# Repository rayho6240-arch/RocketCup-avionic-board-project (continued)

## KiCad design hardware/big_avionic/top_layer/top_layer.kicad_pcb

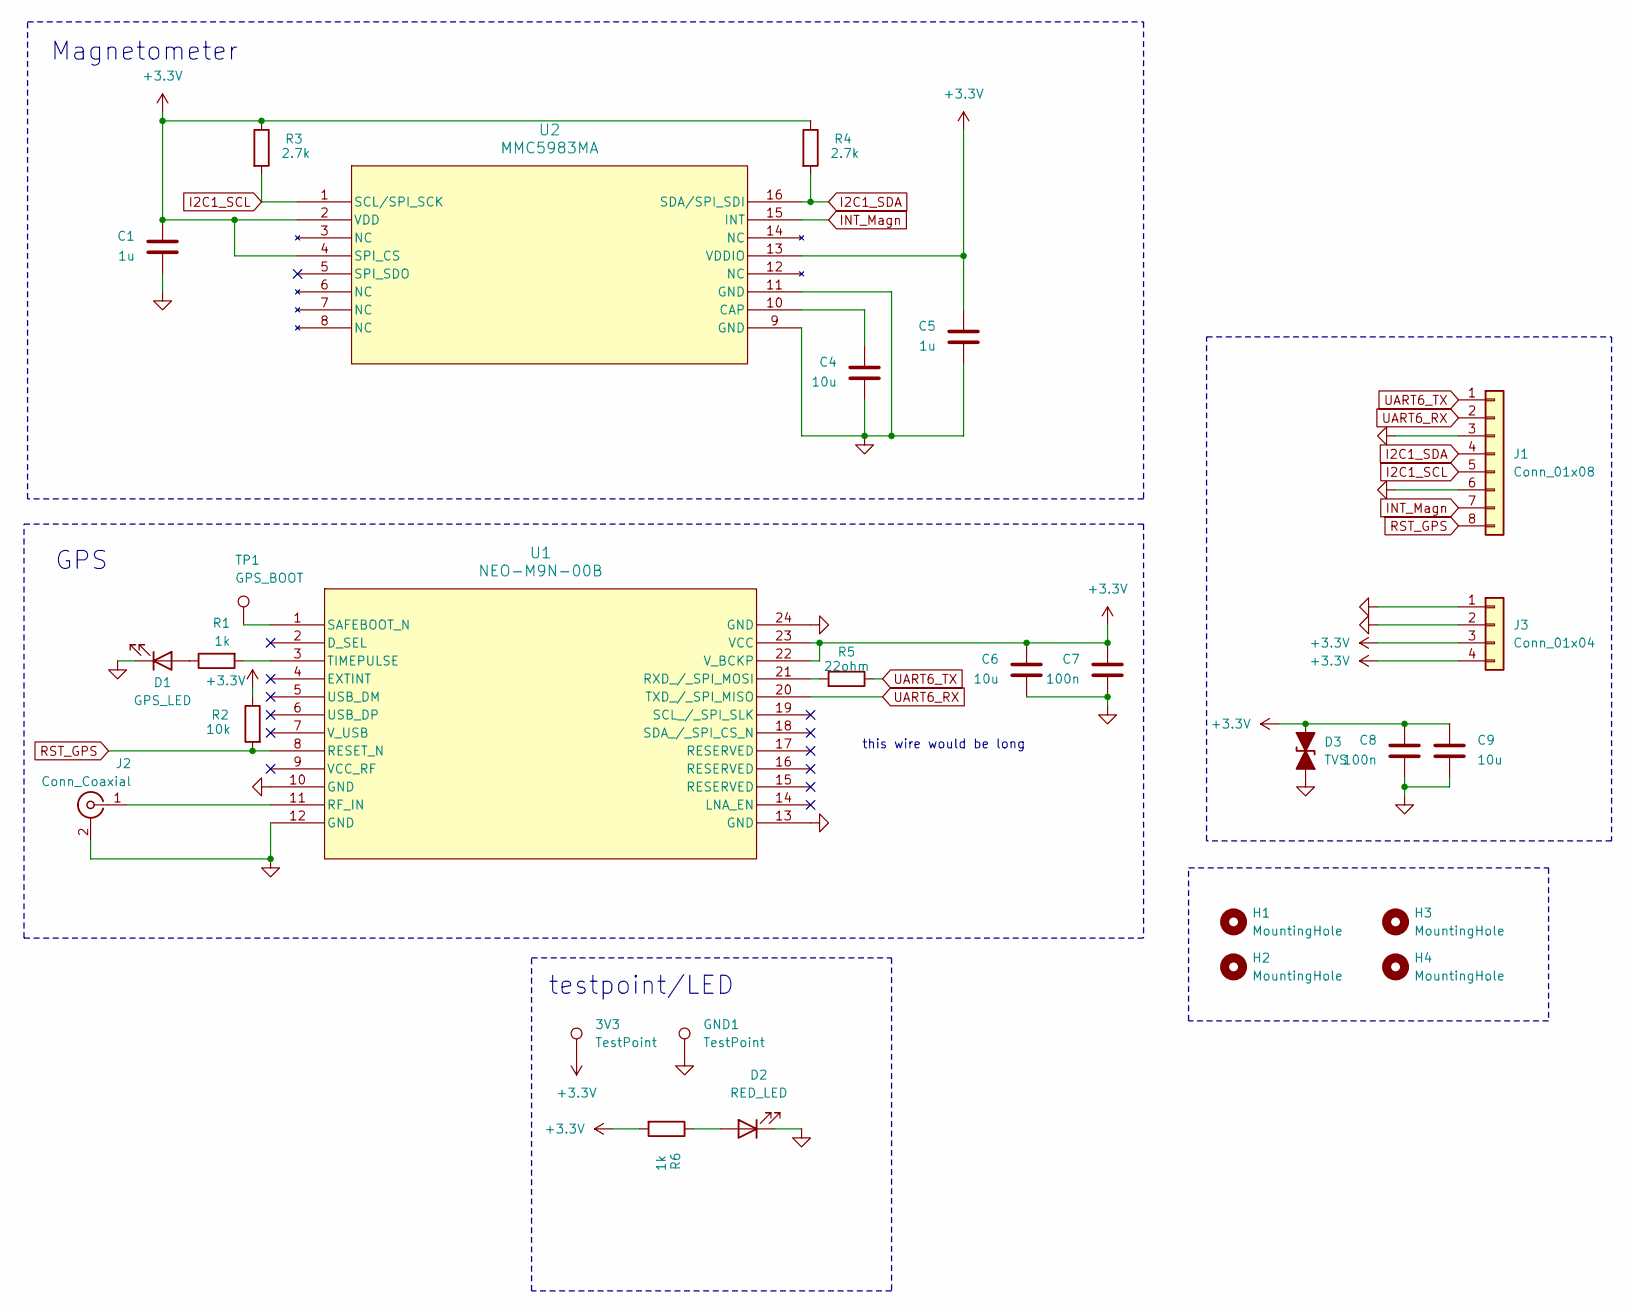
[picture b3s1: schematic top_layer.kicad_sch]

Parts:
3V3: TestPoint; TestPoint_Pad_D1.0mm
C1, C5: 1u; C_0805_2012Metric_Pad1.18x1.45mm_HandSolder
C4, C6, C9: 10u; C_1206_3216Metric_Pad1.33x1.80mm_HandSolder
C7, C8: 100n; C_0805_2012Metric_Pad1.18x1.45mm_HandSolder
D1: GPS_LED; LED_0805_2012Metric_Pad1.15x1.40mm_HandSolder
D2: RED_LED; LED_0805_2012Metric_Pad1.15x1.40mm_HandSolder
D3: TVS; D_SMA
GND1: TestPoint; TestPoint_Pad_D1.0mm
H1, H2, H3, H4: MountingHole; MountingHole_3.2mm_M3_DIN965_Pad
J1: Conn_01x08; JST_GH_SM08B-GHS-TB_1x08-1MP_P1.25mm_Horizontal
J2: Conn_Coaxial; U.FL_Hirose_U.FL-R-SMT-1_Vertical
J3: Conn_01x04; JST_GH_SM04B-GHS-TB_1x04-1MP_P1.25mm_Horizontal
R1, R6: 1k; R_0805_2012Metric_Pad1.20x1.40mm_HandSolder
R2: 10k; R_0805_2012Metric_Pad1.20x1.40mm_HandSolder
R3, R4: 2.7k; R_0805_2012Metric_Pad1.20x1.40mm_HandSolder
R5: 22ohm; R_0805_2012Metric_Pad1.20x1.40mm_HandSolder
TP1: GPS_BOOT; TestPoint_Pad_D1.0mm
U1: NEO-M9N-00B; SMT_9N-00B_UBL
U2: MMC5983MA; MMC5983MA_MEM

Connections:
+3.3V: 3V3.1, C1.1, C5.1, C6.1, C7.1, C8.1, C9.1, D3.2 (A2), J3.3, J3.4, R2.1, R3.1, R4.1, R6.2, U1.22 (V_BCKP), U1.23 (VCC), U2.2 (VDD), U2.4 (SPI_CS), U2.13 (VDDIO)
GND: C1.2, C4.2, C5.2, C6.2, C7.2, C8.2, C9.2, D1.1 (K), D2.1 (K), D3.1 (A1), GND1.1, J1.3, J1.6, J2.2 (Ext), J3.1, J3.2, U1.10 (GND), U1.12 (GND), U1.13 (GND), U1.24 (GND), U2.9 (GND), U2.11 (GND)
I2C1_SCL: J1.5, R3.2, U2.1 (SCL/SPI_SCK)
I2C1_SDA: J1.4, R4.2, U2.16 (SDA/SPI_SDI)
INT_Magn: J1.7, U2.15 (INT)
unnamed: D1.2 (A), R1.1
unnamed: D2.2 (A), R6.1
unnamed: J2.1 (In), U1.11 (RF_IN)
unnamed: R5.2, U1.21 (RXD_/_SPI_MOSI)
unnamed: TP1.1, U1.1 (SAFEBOOT_N)
unnamed: R1.2, U1.3 (TIMEPULSE)
unnamed: C4.1, U2.10 (CAP)
RST_GPS: J1.8, R2.2, U1.8 (RESET_N)
UART6_RX: J1.2, U1.20 (TXD_/_SPI_MISO)
UART6_TX: J1.1, R5.1

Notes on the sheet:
testpoint/LED
Magnetometer
this wire would be long
GPS

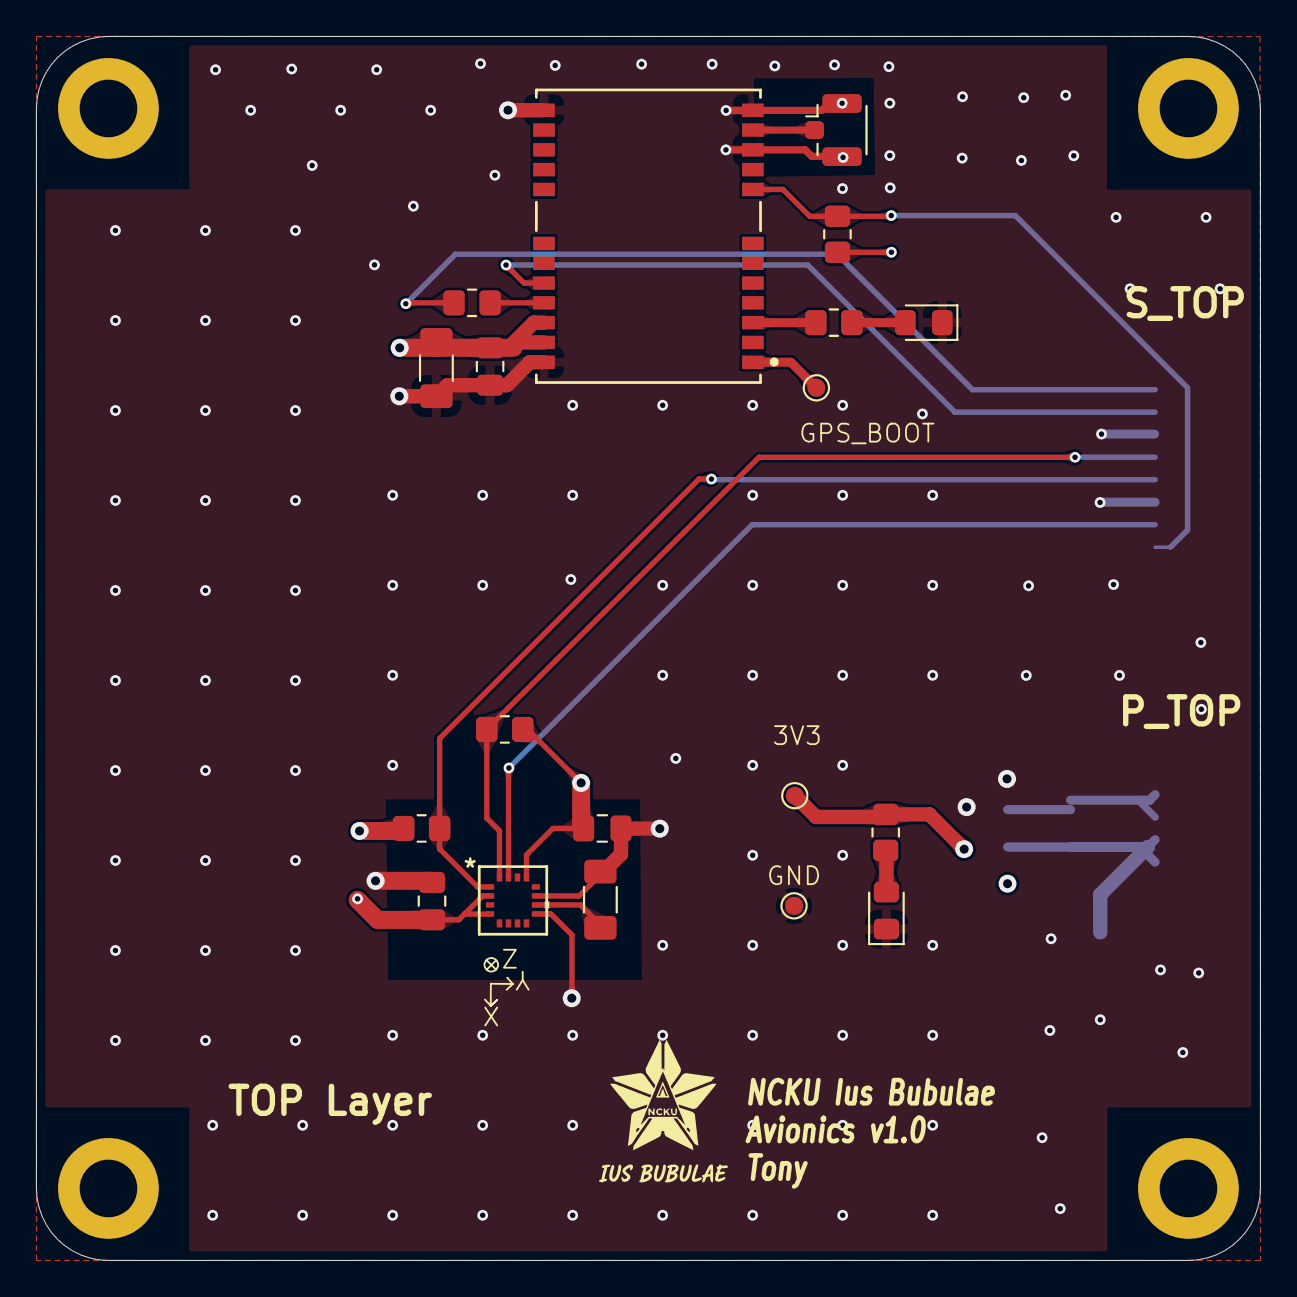
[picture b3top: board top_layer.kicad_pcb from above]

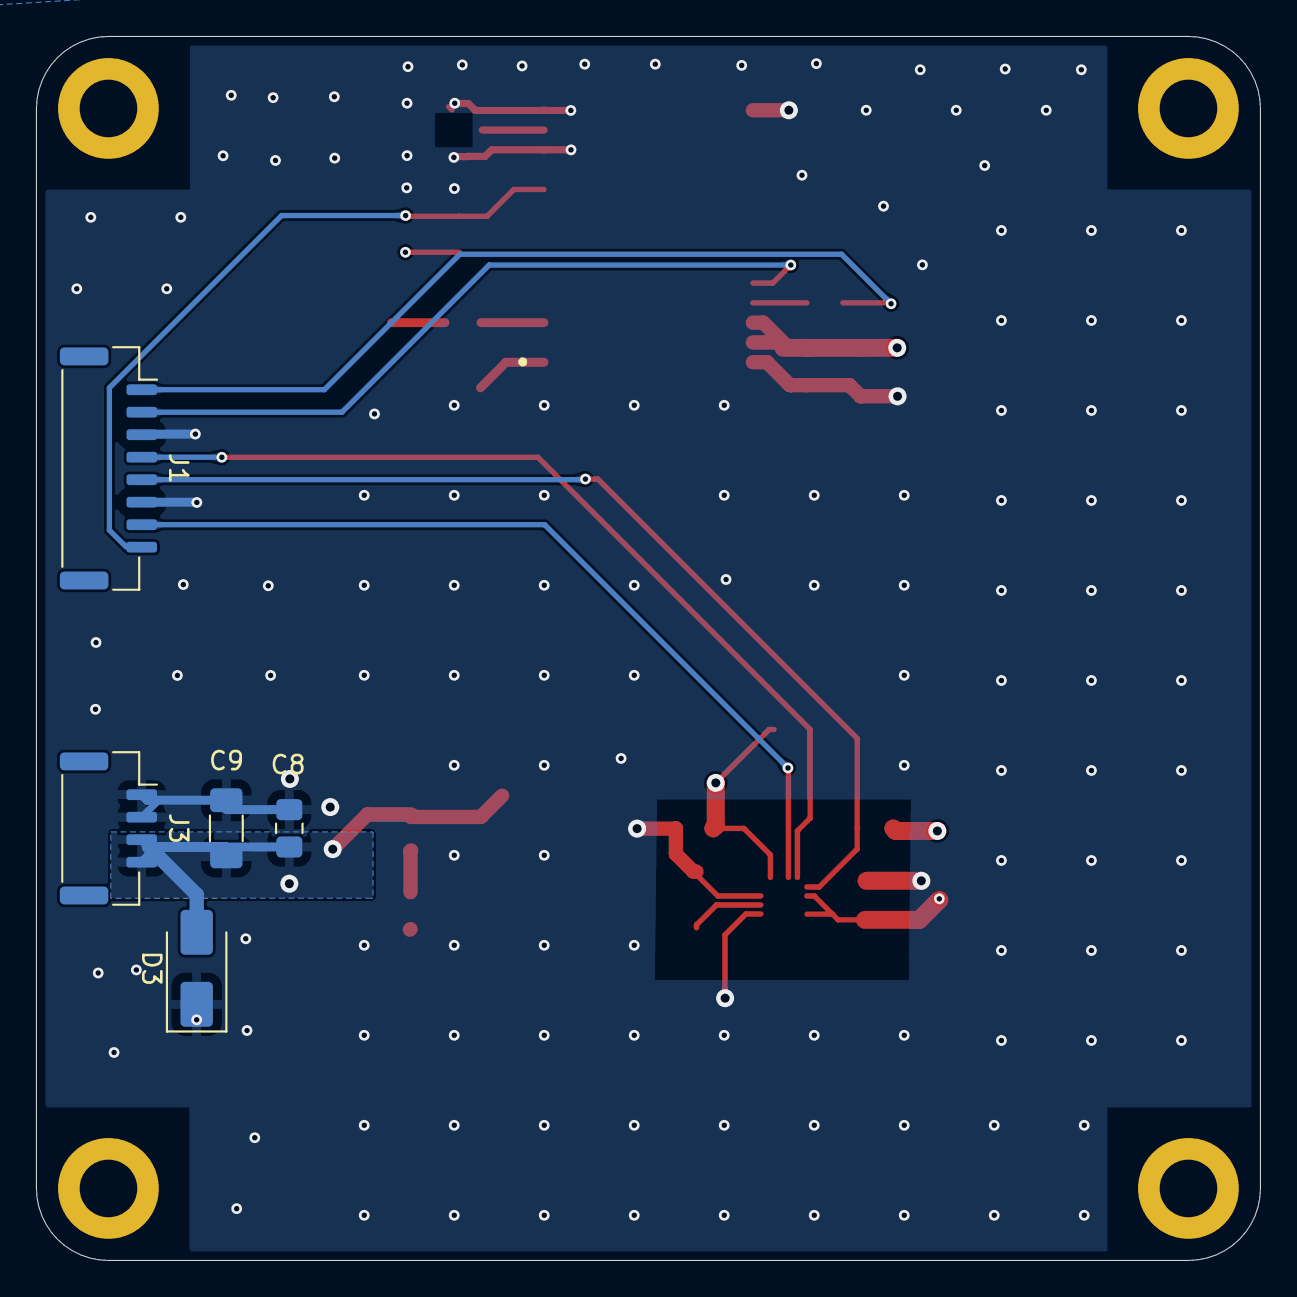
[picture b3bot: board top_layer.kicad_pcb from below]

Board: 4 copper layers, 68.0 x 68.0 mm, 28 parts (5 on the bottom side), 15 nets.

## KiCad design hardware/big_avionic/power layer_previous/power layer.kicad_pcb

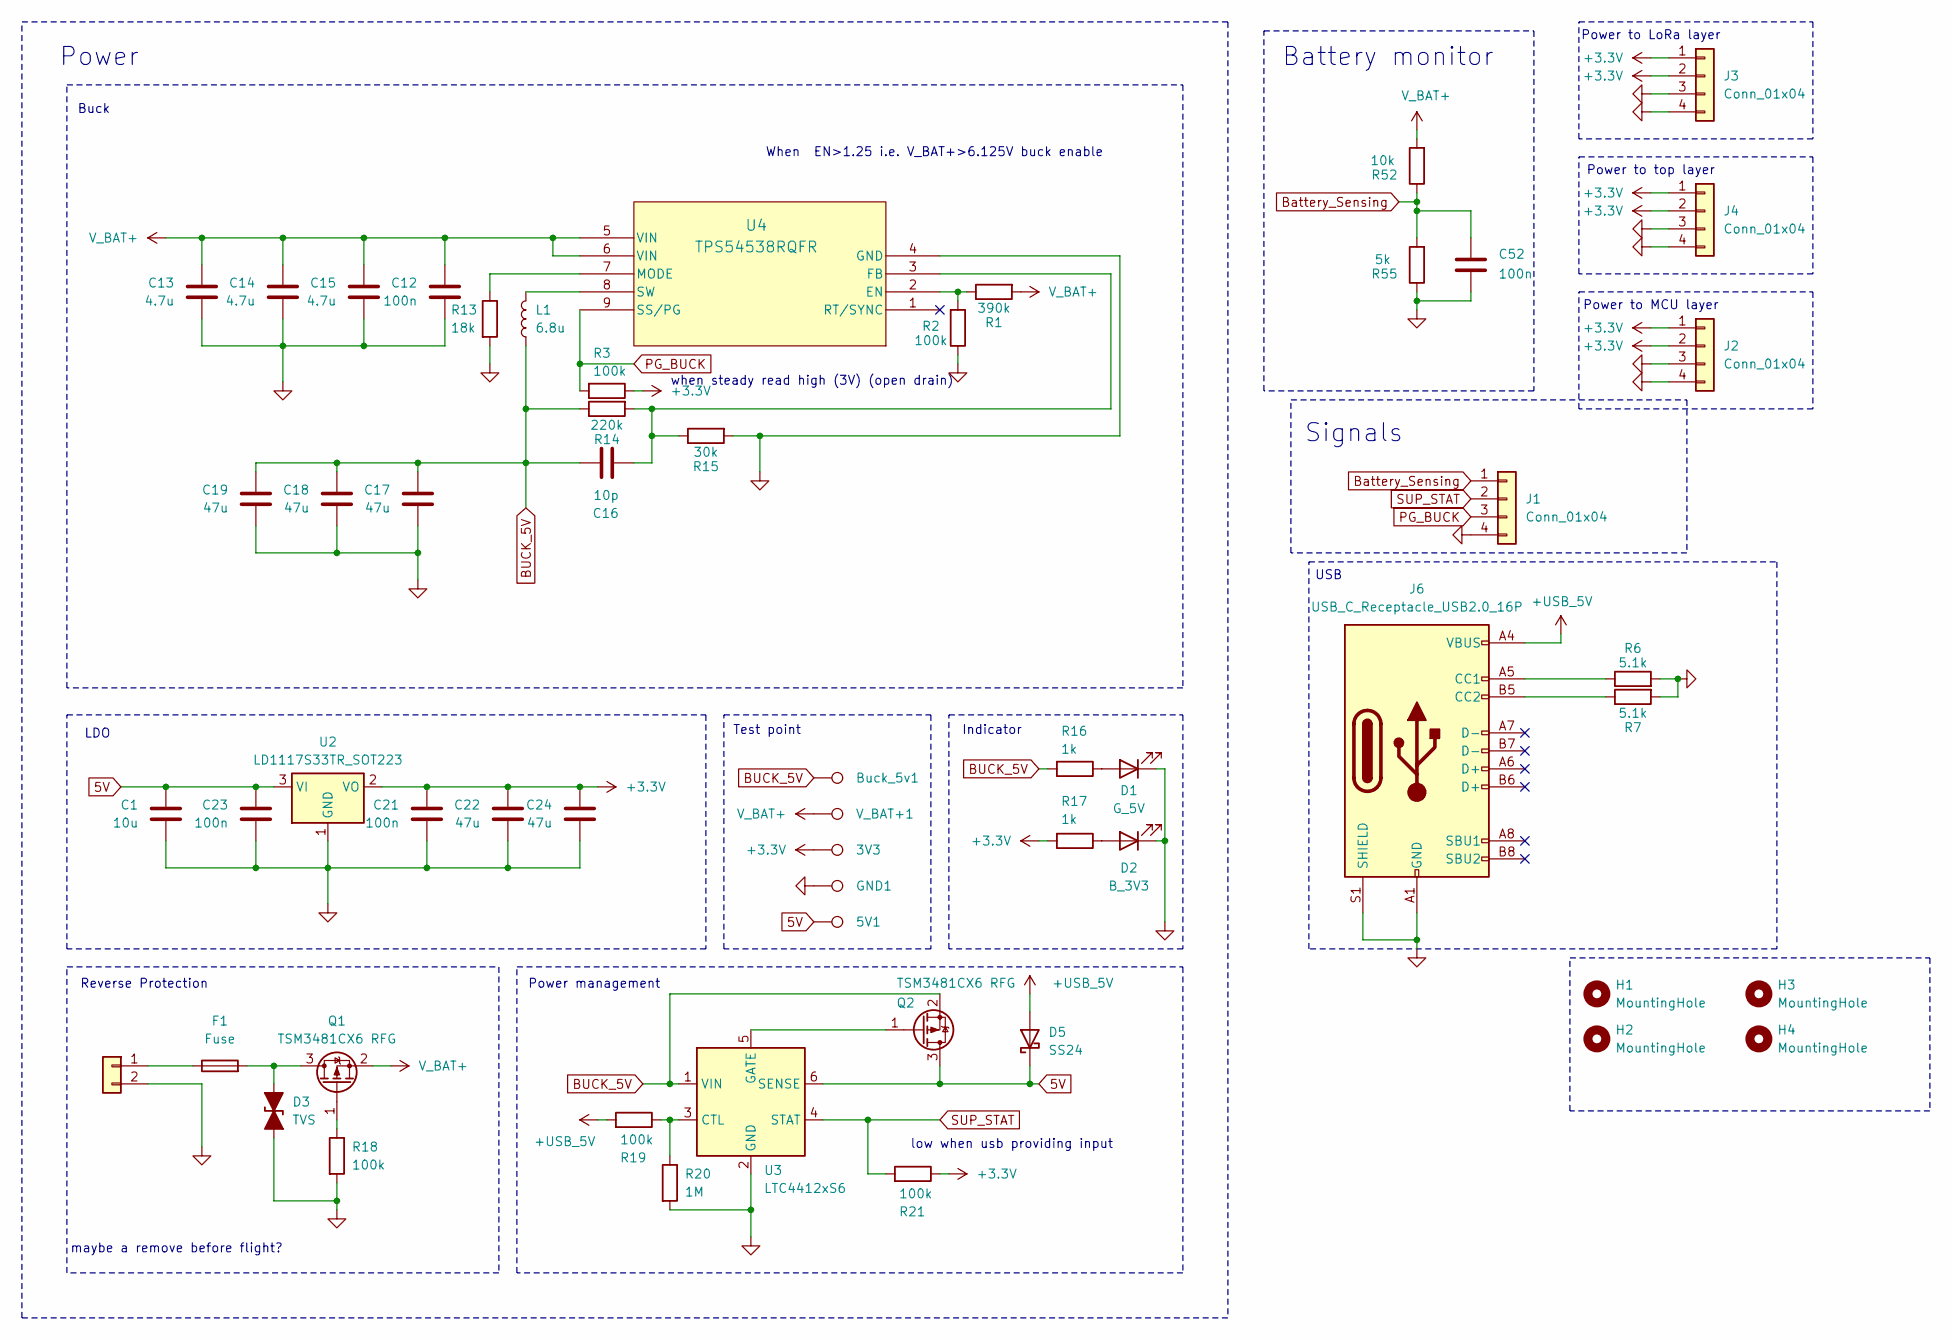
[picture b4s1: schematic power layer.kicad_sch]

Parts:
3V3: TestPoint; TestPoint_Pad_D1.0mm
5V1: TestPoint; TestPoint_Pad_1.0x1.0mm
Buck_5v1: TestPoint; TestPoint_Pad_D1.0mm
C1: 10u; C_0805_2012Metric_Pad1.18x1.45mm_HandSolder
C12: 100n; C_0603_1608Metric_Pad1.08x0.95mm_HandSolder
C13, C14, C15: 4.7u; C_1206_3216Metric_Pad1.33x1.80mm_HandSolder
C16: 10p; C_0402_1005Metric_Pad0.74x0.62mm_HandSolder
C17, C18, C19, C22, C24: 47u; C_1206_3216Metric_Pad1.33x1.80mm_HandSolder
C21, C23, C52: 100n; C_0805_2012Metric_Pad1.18x1.45mm_HandSolder
D1: G_5V; LED_0805_2012Metric_Pad1.15x1.40mm_HandSolder
D2: B_3V3; LED_0805_2012Metric_Pad1.15x1.40mm_HandSolder
D3: TVS; LED_0805_2012Metric_Pad1.15x1.40mm_HandSolder
D5: SS24; D_SMA
F1: Fuse; Fuse_0805_2012Metric_Pad1.15x1.40mm_HandSolder
GND1: TestPoint; TestPoint_Pad_1.0x1.0mm
H1, H2, H3, H4: MountingHole; MountingHole_3.2mm_M3_DIN965_Pad
J1, J2, J3, J4: Conn_01x04; JST_GH_SM04B-GHS-TB_1x04-1MP_P1.25mm_Horizontal
J5: Conn_01x02; JST_PH_S2B-PH-K_1x02_P2.00mm_Horizontal
J6: USB_C_Receptacle_USB2.0_16P; USB_C_Receptacle_HRO_TYPE-C-31-M-12
L1: 6.8u; L_7.3x7.3_H3.5
Q1, Q2: TSM3481CX6 RFG; SOT-23
R1: 390k; C_0603_1608Metric_Pad1.08x0.95mm_HandSolder
R2, R3, R18, R19, R21: 100k; C_0603_1608Metric_Pad1.08x0.95mm_HandSolder
R6, R7: 5.1k; R_0805_2012Metric_Pad1.20x1.40mm_HandSolder
R13: 18k; C_0603_1608Metric_Pad1.08x0.95mm_HandSolder
R14: 220k; C_0603_1608Metric_Pad1.08x0.95mm_HandSolder
R15: 30k; C_0603_1608Metric_Pad1.08x0.95mm_HandSolder
R16, R17: 1k; C_0603_1608Metric_Pad1.08x0.95mm_HandSolder
R20: 1M; C_0603_1608Metric_Pad1.08x0.95mm_HandSolder
R52: 10k; C_0603_1608Metric_Pad1.08x0.95mm_HandSolder
R55: 5k; C_0603_1608Metric_Pad1.08x0.95mm_HandSolder
U2: LD1117S33TR_SOT223; SOT-223-3_TabPin2
U3: LTC4412xS6; TSOT-23-6
U4: TPS54538RQFR; VQFN-HR9_RQF_TEX(TPS54538)
V_BAT+1: TestPoint; TestPoint_Pad_D1.0mm

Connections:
5V: 5V1.1, C1.1, C23.1, D5.1 (K), Q2.3 (D), U2.3 (VI), U3.6 (SENSE)
+3.3V: 3V3.1, C21.1, C22.1, C24.1, J2.1, J2.2, J3.1, J3.2, J4.1, J4.2, R3.1, R17.2, R21.1, U2.2 (VO)
+USB_5V: D5.2 (A), J6.A4 (VBUS), J6.A9 (VBUS), J6.B4 (VBUS), J6.B9 (VBUS), R19.2
BUCK_5V: Buck_5v1.1, C16.1, C17.1, C18.1, C19.1, L1.1, Q2.2 (S), R14.1, R16.2, U3.1 (VIN)
Battery_Sensing: C52.1, J1.1, R52.1, R55.2
GND: C1.2, C12.2, C13.2, C14.2, C15.2, C17.2, C18.2, C19.2, C21.2, C22.2, C23.2, C24.2, C52.2, D1.1 (K), D2.1 (K), D3.1 (A1), GND1.1, J1.4, J2.3, J2.4, J3.3, J3.4, J4.3, J4.4, J5.2, J6.A1 (GND), J6.A12 (GND), J6.B1 (GND), J6.B12 (GND), J6.S1 (SHIELD), R2.1, R6.2, R7.2, R13.2, R15.2, R18.2, R20.2, R55.1, U2.1 (GND), U3.2 (GND), U4.4 (GND)
unnamed: D1.2 (A), R16.1
unnamed: D2.2 (A), R17.1
unnamed: D3.2 (A2), F1.2, Q1.3 (D)
unnamed: F1.1, J5.1
unnamed: J6.A5 (CC1), R6.1
unnamed: J6.B5 (CC2), R7.1
unnamed: Q1.1 (G), R18.1
unnamed: Q2.1 (G), U3.5 (GATE)
unnamed: R19.1, R20.1, U3.3 (CTL)
unnamed: R1.1, R2.2, U4.2 (EN)
unnamed: C16.2, R14.2, R15.1, U4.3 (FB)
unnamed: R13.1, U4.7 (MODE)
unnamed: L1.2, U4.8 (SW)
PG_BUCK: J1.3, R3.2, U4.9 (SS/PG)
SUP_STAT: J1.2, R21.2, U3.4 (STAT)
V_BAT+: C12.1, C13.1, C14.1, C15.1, Q1.2 (S), R1.2, R52.2, U4.5 (VIN), U4.6 (VIN), V_BAT+1.1

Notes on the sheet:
LDO
Indicator
Power management
USB
Buck
maybe a remove before flight?
Power to MCU layer
Signals
Reverse Protection
Test point
low when usb providing input
Battery monitor
Power
When EN>1.25 i.e. V_BAT+>6.125V buck enable
Power to top layer
Power to LoRa layer
when steady read high (3V) (open drain)

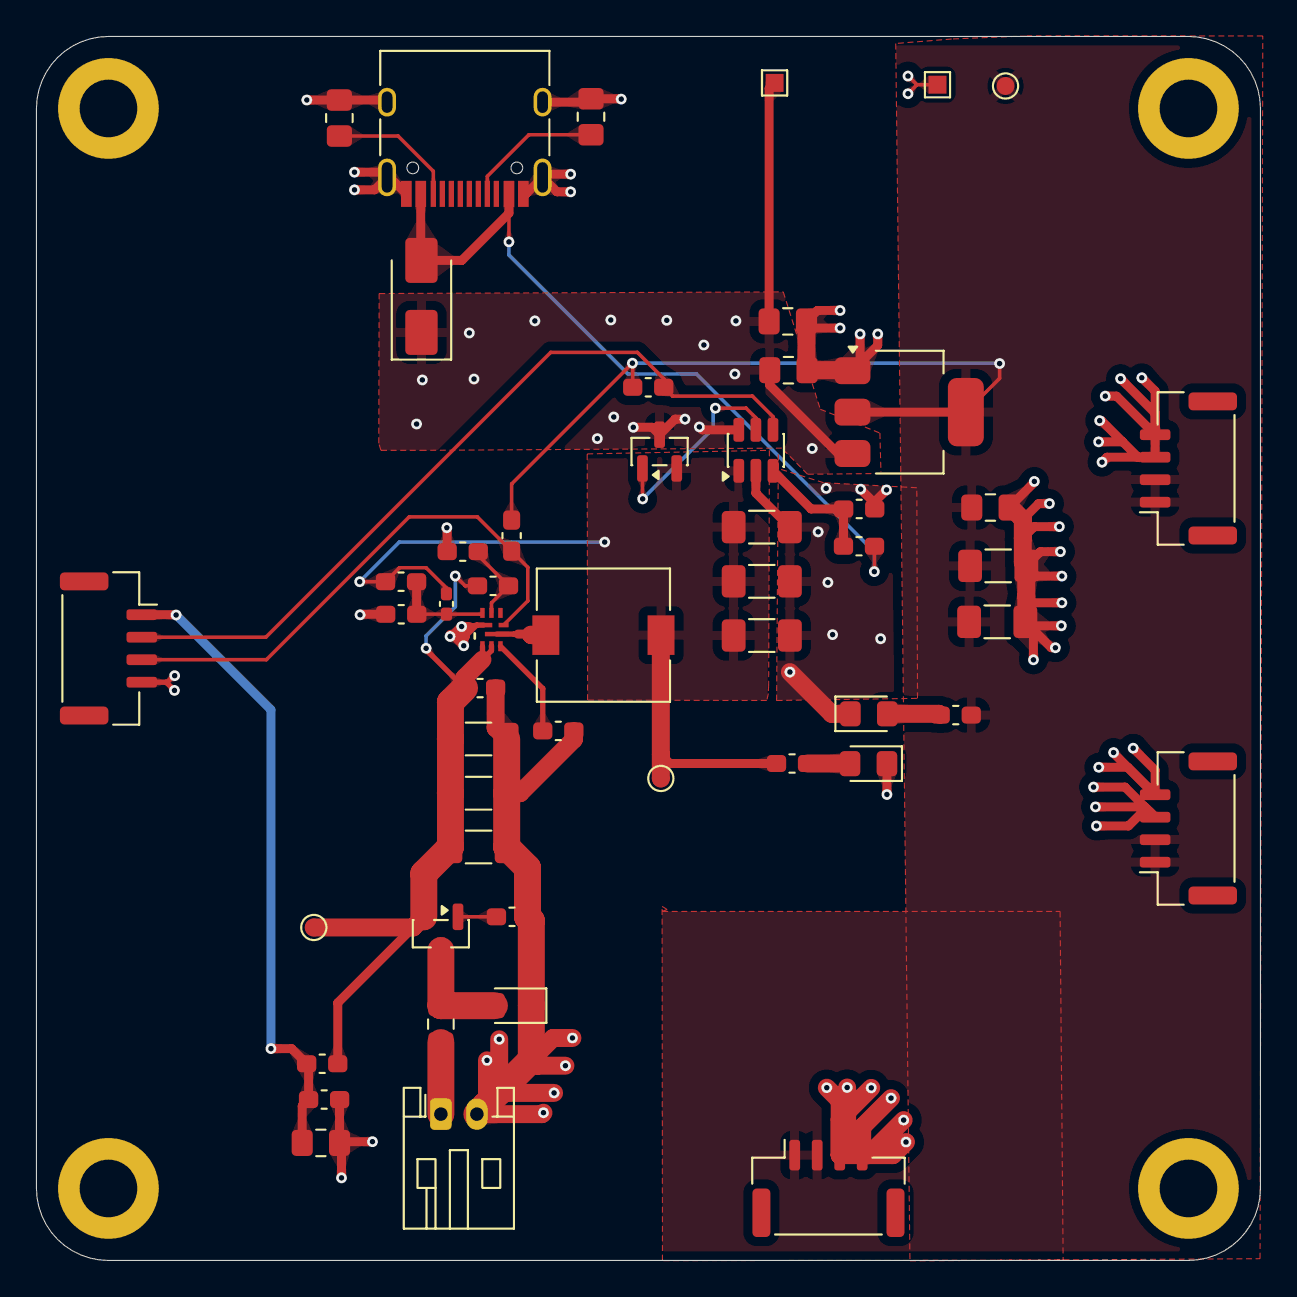
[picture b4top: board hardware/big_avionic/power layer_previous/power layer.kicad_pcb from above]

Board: 4 copper layers, 68.0 x 68.0 mm, 56 parts (0 on the bottom side), 22 nets.

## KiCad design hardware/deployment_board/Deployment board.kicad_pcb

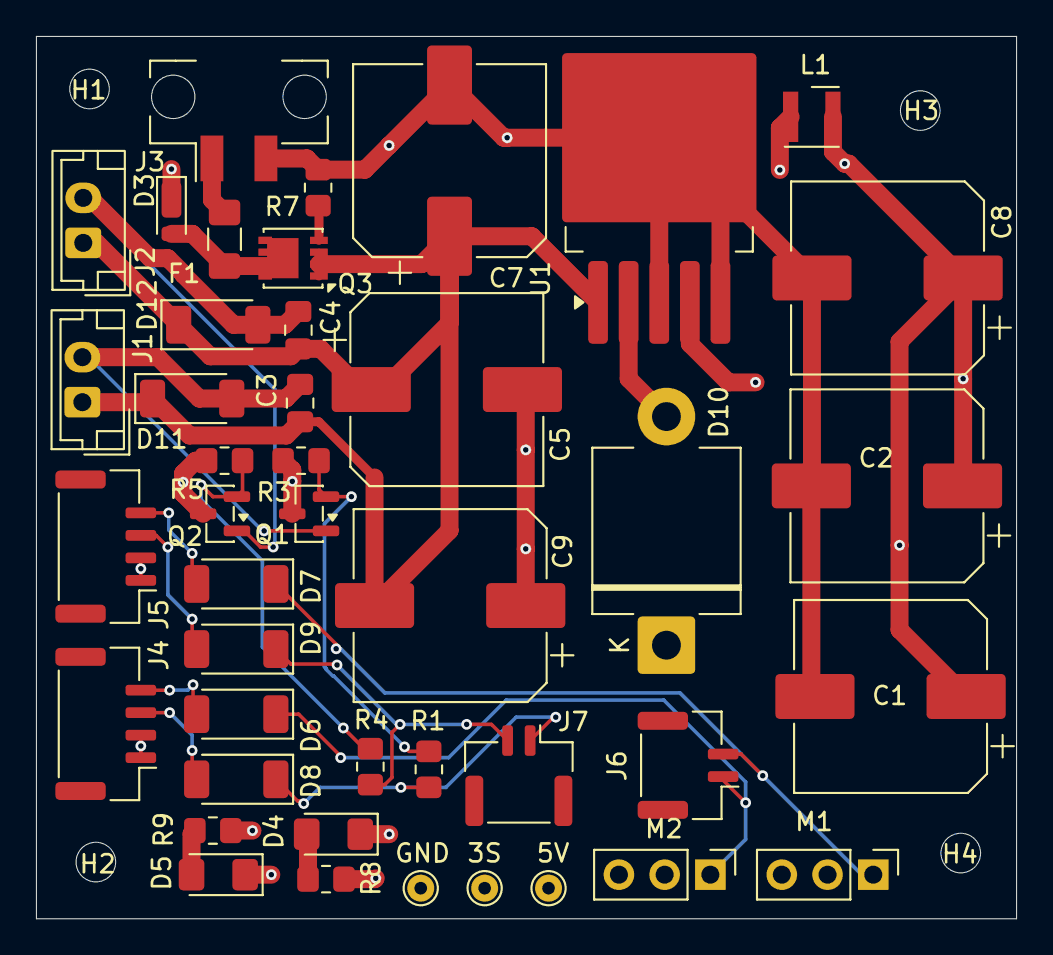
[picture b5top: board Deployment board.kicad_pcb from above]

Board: 4 copper layers, 54.5 x 49.0 mm, 47 parts (0 on the bottom side), 21 nets.

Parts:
3S, 5V: TestPoint; TestPoint_THTPad_D1.5mm_Drill0.7mm
C1, C2, C5, C7, C8, C9: 220uF,865060657012; CP_Elec_10x10.5
C3, C4: 100n,CX0805MRX7R7BB104; C_0805_2012Metric_Pad1.18x1.45mm_HandSolder
D3: TVS,VS15VUA1VWMTFTR; D_TUMD2
D4, D5: LED,AP3216ID; LED_1206_3216Metric_Pad1.42x1.75mm_HandSolder
D6, D7, D8, D9, D11, D12: D_Schottky,PMEG3030EP,115; D_SOD-128
D10: 1N5824; D_5KPW_P12.70mm_Horizontal
F1: Fuse,CC12H15A-TR; Fuse_1206_3216Metric_Pad1.42x1.75mm_HandSolder
GND: TestPoint; TestPoint_THTPad_D1.5mm_Drill0.7mm
H1, H2, H3, H4: MountingHole; MountingHole_2.2mm_M2
J1, J2: Conn_01x02; JST_EH_B2B-EH-A_1x02_P2.50mm_Vertical
J3: Conn_01x02; Molex_Micro-Fit_3.0_43650-0221_1x02_P3.00mm_Vertical
J4, J5: Conn_01x04; JST_GH_BM04B-GHS-TBT_1x04-1MP_P1.25mm_Vertical
J6, J7: Conn_01x02; JST_GH_BM02B-GHS-TBT_1x02-1MP_P1.25mm_Vertical
L1: 33uH,SRN3010BTA-330M; L_Wurth_WE-LQSH-3012
M1, M2: Motor_Servo; PinHeader_1x03_P2.54mm_Vertical
Q1, Q2: IRLML6344TRPBF; SOT-23
Q3: SI7613DN-T1-GE3; Vishay_PowerPAK_1212-8_Single
R1, R4: 220 ohm,1/8W,RG2012P-221-B-T5; R_0805_2012Metric_Pad1.20x1.40mm_HandSolder
R3, R5: 1k,SR0805FR-7W1KL; R_0805_2012Metric_Pad1.20x1.40mm_HandSolder
R7: 100k; R_0805_2012Metric_Pad1.20x1.40mm_HandSolder
R8: 560ohm 1/2W,ERJ-UP6D5600V; R_0805_2012Metric_Pad1.20x1.40mm_HandSolder
R9: 180ohm 1/4W,CRCW0805180RFKEA; R_0805_2012Metric_Pad1.20x1.40mm_HandSolder
U1: LM2596S-5.0/NOPB; TO-263-5_TabPin3

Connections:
2sServo1: D7.1 (K), J6.2, M1.1 (PWM)
2sServo2: D6.1 (K), J6.1, M2.1 (PWM)
3s+: 3S.1 (1_1), C3.2, C4.2, C5.1, C7.1, C9.2, D11.1 (K), D12.1 (K), J1.1, J2.1, Q3.1 (S), Q3.2 (S), Q3.3 (S), R8.2, U1.1 (VIN)
3sMotor1: D9.1 (K), J7.2, R4.2
3sMotor2: D8.1 (K), J7.1, R1.2
5V+: 5V.1 (1_1), C1.1, C2.1, C8.1, L1.2, M1.2 (+), M2.2 (+), R9.2, U1.4 (FEEDBACK)
Backup_AV_FIRE: D9.2 (A), J5.3
Backup_AV_PWM_Servo: D7.2 (A), J5.4
GND: C1.2, C2.2, C5.2, C7.2, C8.2, C9.1, D3.1 (A1), D4.1 (K), D5.1 (K), D10.1 (K), GND.1 (1_1), J3.2, J4.1, J4.2, J5.1, J5.2, M1.3 (-), M2.3 (-), Q1.3 (S), Q2.3 (S), R3.2, R5.2, R7.2, U1.3 (GND), U1.5 (ON_OFF_N)
Main_AV_FIRE: D8.2 (A), J4.3
Main_AV_PWM_Servo: D6.2 (A), J4.4
unnamed: D3.2 (A2), F1.2, Q3.5 (D)
unnamed: D4.2 (A), R8.1
unnamed: D5.2 (A), R9.1
unnamed: D10.2 (A), L1.1, U1.2 (OUTPUT)
unnamed: C3.1, D11.2 (A), J1.2, Q1.1 (D)
unnamed: C4.1, D12.2 (A), J2.2, Q2.1 (D)
unnamed: F1.1, J3.1
unnamed: Q1.2 (G), R1.1, R3.1
unnamed: Q2.2 (G), R4.1, R5.1
unnamed: Q3.4 (G), R7.1

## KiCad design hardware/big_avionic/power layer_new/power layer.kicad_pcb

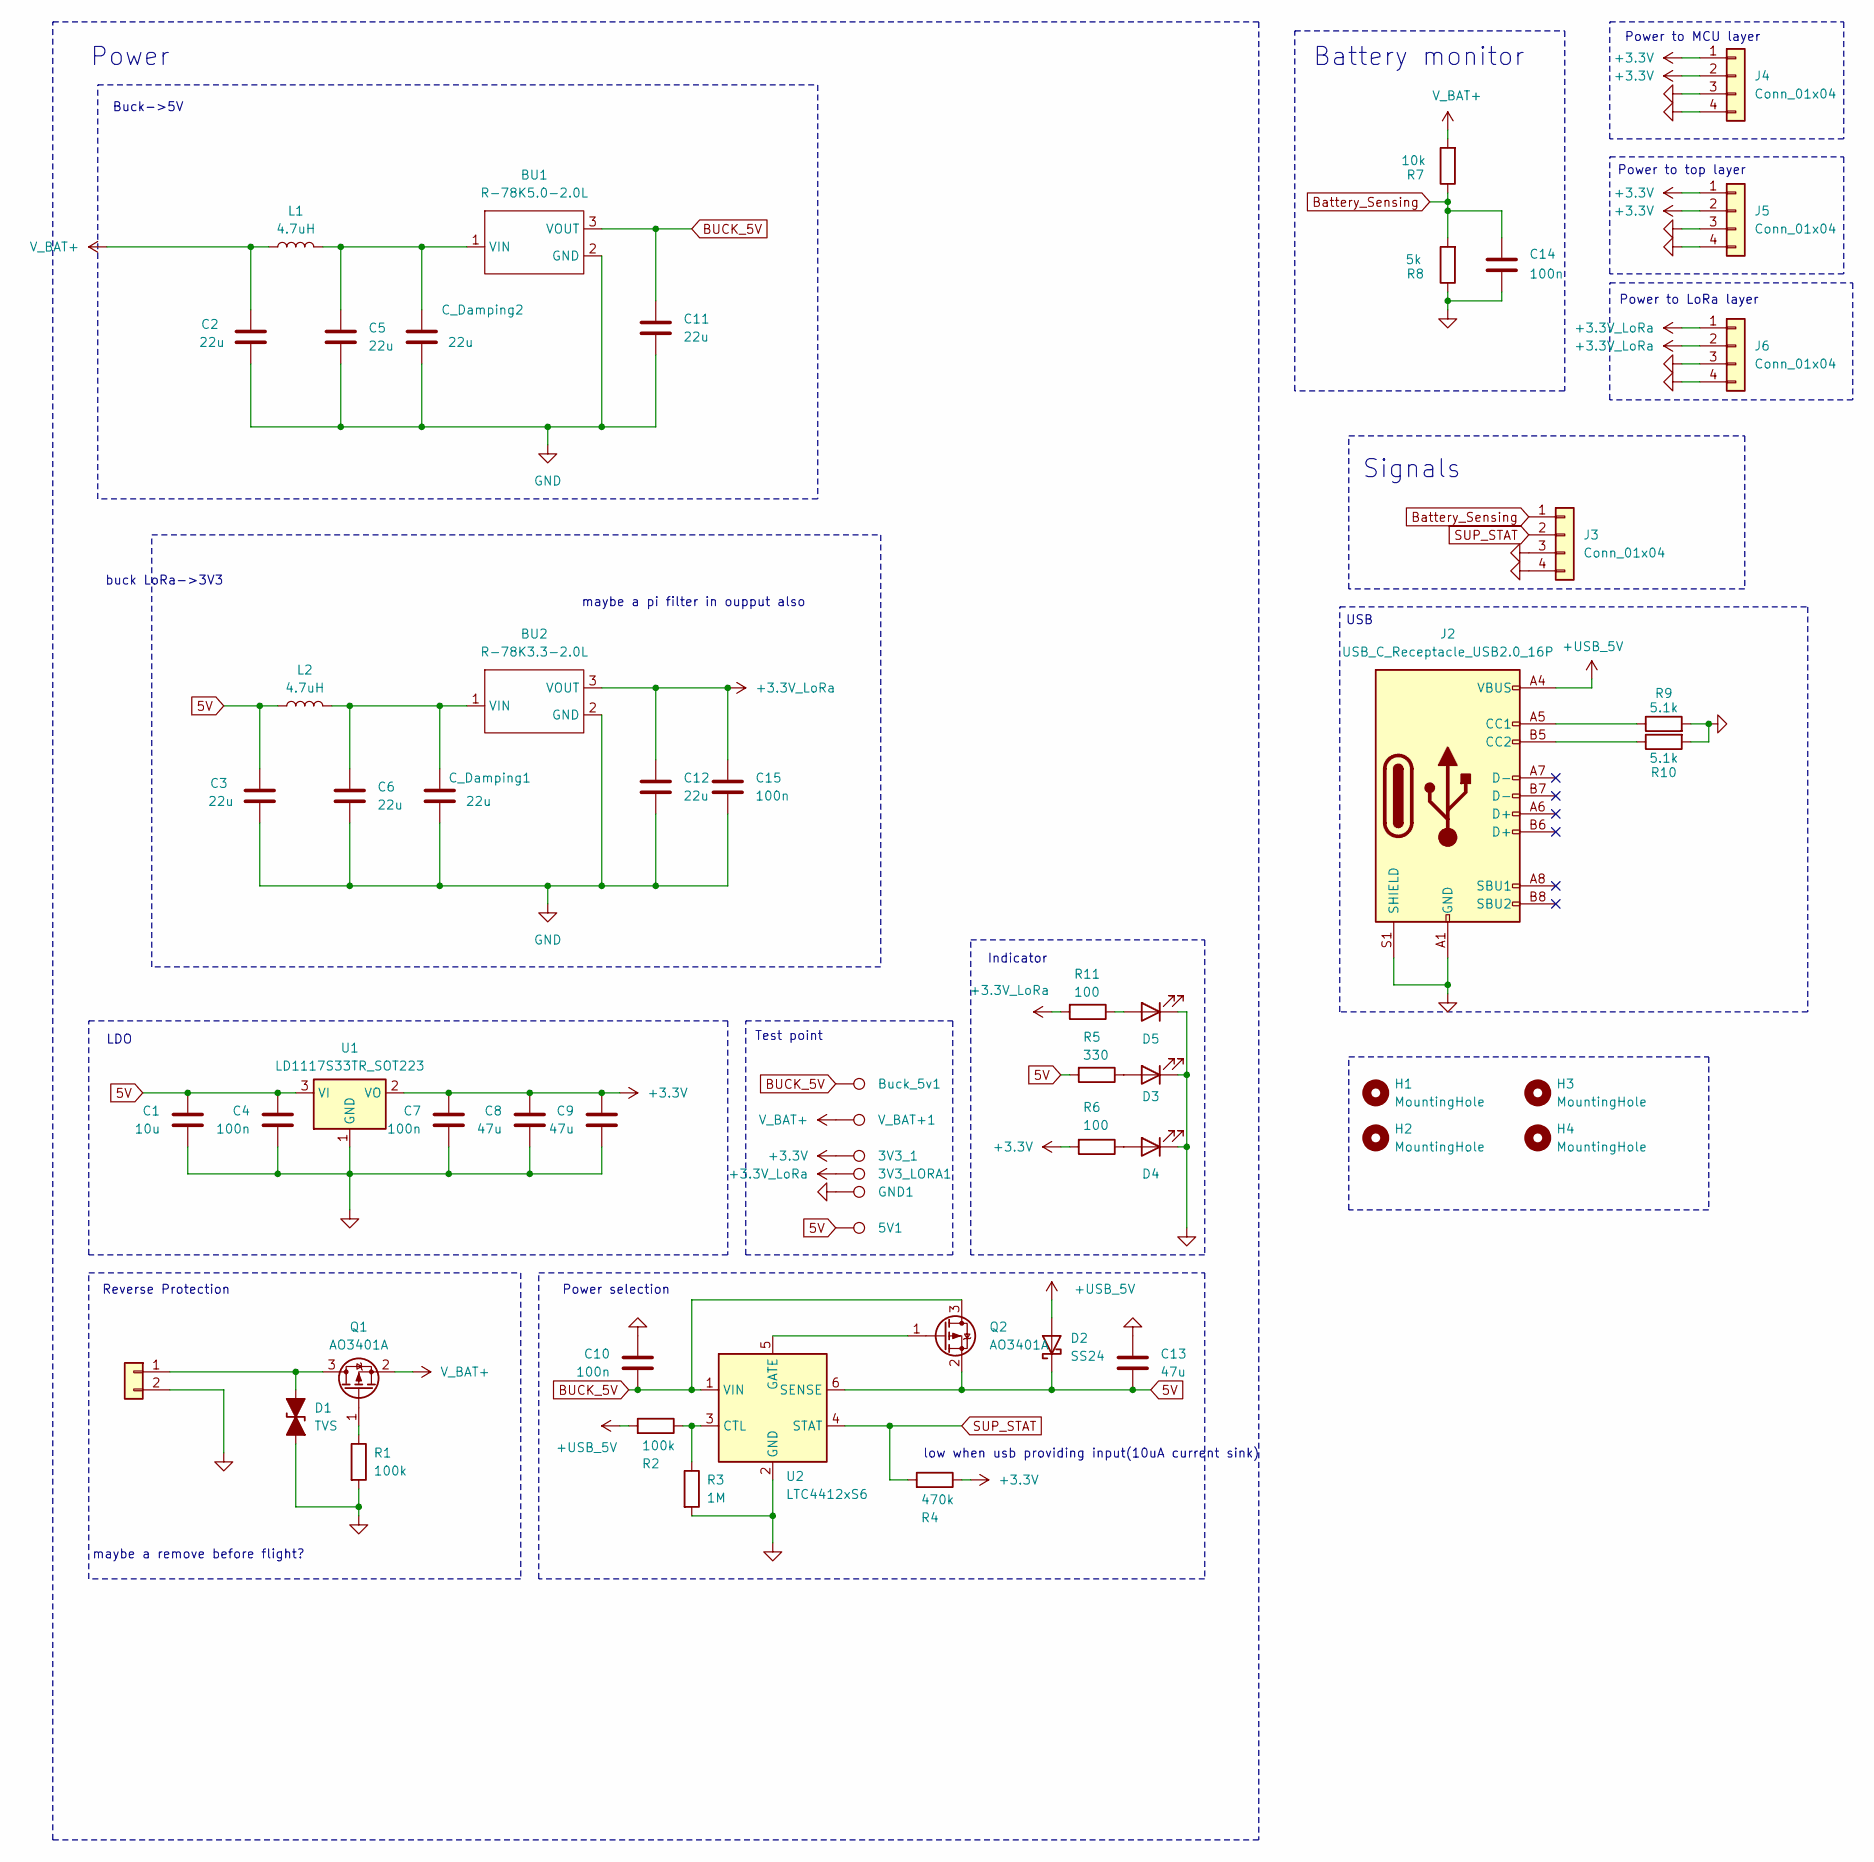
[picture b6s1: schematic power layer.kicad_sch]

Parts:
3V3_1, 3V3_LORA1, 5V1: TestPoint; TestPoint_Pad_D1.0mm
BU1: R-78K5.0-2.0L; CONV_R-78K5.0-2.0L
BU2: R-78K3.3-2.0L; CONV_R-78K5.0-2.0L
Buck_5v1: TestPoint; TestPoint_Pad_D1.0mm
C1: 10u; C_1210_3225Metric_Pad1.33x2.70mm_HandSolder
C2, C3, C5, C6, C11, C12: 22u; C_1210_3225Metric_Pad1.33x2.70mm_HandSolder
C4, C7, C10, C14, C15: 100n; C_0805_2012Metric_Pad1.18x1.45mm_HandSolder
C8, C9, C13: 47u; C_1210_3225Metric_Pad1.33x2.70mm_HandSolder
C_Damping1, C_Damping2: 22u; CP_EIA-3528-21_Kemet-B_HandSolder
D1: TVS; D_SMA
D2: SS24; D_SMA
D3, D4, D5: LED_0805_2012Metric_Pad1.15x1.40mm_HandSolder
GND1: TestPoint; TestPoint_Pad_D1.0mm
H1, H2, H3, H4: MountingHole; MountingHole_3.2mm_M3_DIN965_Pad
J1: Conn_01x02; JST_PH_S2B-PH-K_1x02_P2.00mm_Horizontal
J2: USB_C_Receptacle_USB2.0_16P; USB_C_Receptacle_HRO_TYPE-C-31-M-12
J3, J4, J5, J6: Conn_01x04; JST_GH_SM04B-GHS-TB_1x04-1MP_P1.25mm_Horizontal
L1, L2: 4.7uH; L_APV_ANR4020
Q1, Q2: AO3401A; SOT-23
R1, R2: 100k; R_0805_2012Metric_Pad1.20x1.40mm_HandSolder
R3: 1M; R_0805_2012Metric_Pad1.20x1.40mm_HandSolder
R4: 470k; R_0805_2012Metric_Pad1.20x1.40mm_HandSolder
R5: 330; R_0805_2012Metric_Pad1.20x1.40mm_HandSolder
R6, R11: 100; R_0805_2012Metric_Pad1.20x1.40mm_HandSolder
R7: 10k; R_0805_2012Metric_Pad1.20x1.40mm_HandSolder
R8: 5k; R_0805_2012Metric_Pad1.20x1.40mm_HandSolder
R9, R10: 5.1k; R_0805_2012Metric_Pad1.20x1.40mm_HandSolder
U1: LD1117S33TR_SOT223; SOT-223-3_TabPin2
U2: LTC4412xS6; TSOT-23-6
V_BAT+1: TestPoint; TestPoint_Pad_D1.0mm

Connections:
5V: 5V1.1, C1.1, C3.1, C4.1, C13.2, D2.1 (K), L2.1, Q2.2 (S), R5.2, U1.3 (VI), U2.6 (SENSE)
+3.3V: 3V3_1.1, C7.1, C8.1, C9.1, J4.1, J4.2, J5.1, J5.2, R4.1, R6.2, U1.2 (VO)
+3.3V_LoRa: 3V3_LORA1.1, BU2.3 (VOUT), C12.1, C15.1, J6.1, J6.2, R11.2
+USB_5V: D2.2 (A), J2.A4 (VBUS), J2.A9 (VBUS), J2.B4 (VBUS), J2.B9 (VBUS), R2.2
BUCK_5V: BU1.3 (VOUT), Buck_5v1.1, C10.2, C11.1, Q2.3 (D), U2.1 (VIN)
Battery_Sensing: C14.1, J3.1, R7.1, R8.2
GND: BU1.2 (GND), BU2.2 (GND), C1.2, C2.2, C3.2, C4.2, C5.2, C6.2, C7.2, C8.2, C9.2, C10.1, C11.2, C12.2, C13.1, C14.2, C15.2, C_Damping1.2, C_Damping2.2, D1.1 (A1), D3.1 (K), D4.1 (K), D5.1 (K), GND1.1, J1.2, J2.A1 (GND), J2.A12 (GND), J2.B1 (GND), J2.B12 (GND), J2.S1 (SHIELD), J3.3, J3.4, J4.3, J4.4, J5.3, J5.4, J6.3, J6.4, R1.2, R3.2, R8.1, R9.2, R10.2, U1.1 (GND), U2.2 (GND)
unnamed: BU1.1 (VIN), C5.1, C_Damping2.1, L1.2
unnamed: BU2.1 (VIN), C6.1, C_Damping1.1, L2.2
unnamed: D1.2 (A2), J1.1, Q1.3 (D)
unnamed: D3.2 (A), R5.1
unnamed: D4.2 (A), R6.1
unnamed: D5.2 (A), R11.1
unnamed: J2.A5 (CC1), R9.1
unnamed: J2.B5 (CC2), R10.1
unnamed: Q1.1 (G), R1.1
unnamed: Q2.1 (G), U2.5 (GATE)
unnamed: R2.1, R3.1, U2.3 (CTL)
SUP_STAT: J3.2, R4.2, U2.4 (STAT)
V_BAT+: C2.1, L1.1, Q1.2 (S), R7.2, V_BAT+1.1

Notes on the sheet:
LDO
Indicator
maybe a pi filter in oupput also
Power selection
USB
Buck->5V
maybe a remove before flight?
buck LoRa->3V3
Power to MCU layer
Signals
Reverse Protection
Test point
low when usb providing input(10uA current sink)
Battery monitor
Power
Power to top layer
Power to LoRa layer

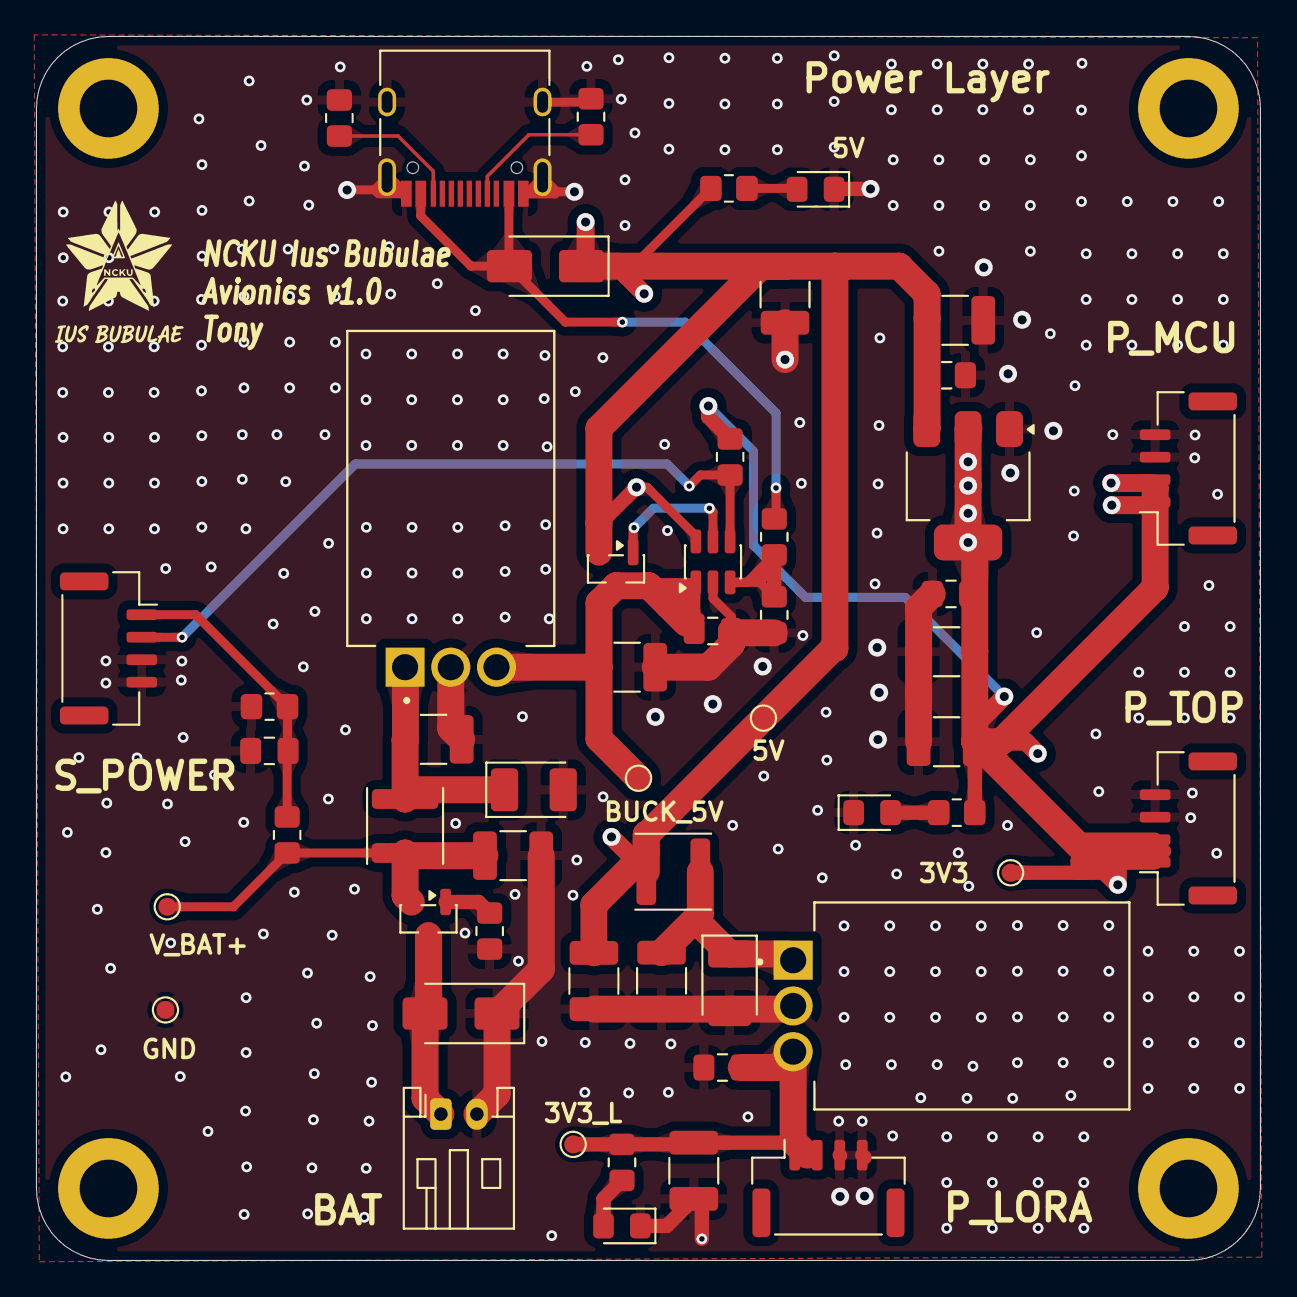
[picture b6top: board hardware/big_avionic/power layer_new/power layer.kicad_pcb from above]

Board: 4 copper layers, 68.0 x 68.0 mm, 57 parts (0 on the bottom side), 20 nets.
